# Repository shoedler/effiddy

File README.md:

# effiddy
A 50-key, column-staggered, wireless split keyboard, inspired by Totem. Designed for Choc-spacing (16.5 by 17.5mm keycaps) and 1350 Choc v1 or v2 switches.

> Kailh Choc v2 Ice Creams, Repo-included 3D printed keycaps

## Effi.. what?
/ˈɛfɪdi/

*effiddy* is a wordplay on **effigy** — a constructed symbolic figure — and *fifty*, referencing the keyboard’s 50 keys.
An **effigy** is a physical representation of an idea, identity, or belief, often ritualistic or iconic in nature.

The design and name are inspired by the **Kindlifresserbrunnen** (Child-Eater Fountain) in Bern, Switzerland:
a striking, unsettling effigy that embodies folklore, symbolism, and cultural memory.
Effiddy adopts this spirit in a minimalist, abstract form — part artifact, part tool.

> **Design note**
> This project came together as a follow up on the [shoedler54](https://github.com/shoedler/shoedler54) split and is also designed entirely in [ergogen.xyz](ergogen.xyz). Since I wanted effiddy to be as thin as possible, I modeled the backside of the case to include cutouts for the SMD components (hotswap sockets, diodes etc.) which resulted in a very thin keyboard, but also an insanely complex ergogen config. The generation of the stl files literally takes minutes when running ergogen through the browser. The reasonable approach to this would've been to use the 3d kicad model of the PCB to model the backplate in CAD. Though, you'd have to model it for both halves due to hotswap socket placement.

## Impressions

---

## Bill of materials

For one complete board - e.g. two halves - you'll need:

- 2 Promicro NRF52840
- 50 1N4148W SOD-123 Diodes
- 50 Kailh Low-profile 1350 Hotswap Sockets
- 50 Keyswitches, Choc v1 or v2
- 50 1u Choc-spaced (16.5x17.5mm) Keycaps, Choc v1 or v2 stem
- 2 EVQPUL02K Switches ($\to$ board reset button)
- 2 SSSS811101 Switches ($\to$ power switch)
- 2 701535 3.7v, 350mAh Batteries
- 2 JST PH 2.0 THT Sockets

For the case you'll need:

- Obviously, the printed case files. See section about printing below.
- 4 M2x3mm heat set inserts.
- 4 M2x6mm (or 8mm) flathead screws
- 8 Stick-on rubber feet

## Build guide

### PCB manufacturing

> PCB related files are located in the `kicad` directory.

I do not suggest rerouting the PCB for fun. There's premade gerber archive located at `kicad/gerber.zip` which you can use. I've used JLCPCB, default settings (1.6mm two layer PCB) and with the black solder mask.

> [!NOTE]
> There's also a 3d render (.stl) of the assembled PCB in the `kicad` directory if you want to model your own case.

### Printing the case

> Case files are located in the `stl` directory.

I used a Babulab A1 mini and default slicer settings (Bambustudio). Everything was printed in their PLA Matte. For a nice effect, I suggest white for the top and keycaps and black for the bottom.

#### What do I need to print?

You'll need at least:

- 2x `effiddy_case_top.stl`, which is the top part of the case where the keyswitches are mounted into - I recommend using the provided 3mf files for that: `effiddy_case_top_left.3mf` and `effiddy_case_top_right.3mf`. Which are mirrored versions with support enabled for the Mcu + Bat enclosures. (Theoretically, bridging works fine, but support is definitely easier and more predictable)
- 1x `effiddy_case_bottom_left.stl`, and
- 1x `effiddy_case_bottom_right.stl`. These are the bottom part of the case - same story, use the provided 3mf files for that: `effiddy_case_bottom_left.3mf` and `effiddy_case_bottom_right.3mf`. These are **not** just mirrored versions. The bottom part of the case is not mirrorable, due to the hotswap sockets being aligned differently for the left and right. 

> [!NOTE]
> The `effiddy_case_bottom_left.stl` and `right.stl` are generated by ergogen. Due to their complexity, they are cursed and a little bit broken. The shape is not closed, there are multiple naked edges, planar and non-planar holes as well as degenerate faces. Despite that, I had no trouble printing it in Bambustudio.

### Printing the keycaps

> Keycap related files are located in the `scad` directory.

The caps require no supports if you place them on one of the fillets - they do however require good bed adhesion. This, just like the case, was also printed on a Bambulab A1 mini with PLA Matte. Also, like the case, I've provided a 3mf file to print regular and indexing (F/J keys on QWERTY) keys. If you have to use the stl directly:

- Use 0.12mm layer height (including the initial layer).
- Use a brim - if your slicer doesn't automatically generate it, add it manually.
- Use a little manually placed support on the face of the keycap. Centered, about 1/3 the way up the slope. In Bambustudio, the slicer will turn this into a small wedge that is just enough to stabilize the cap but not leave any traces of support material on the keycap face.

> [!NOTE]
> The keycap was designed in [OpenSCAD](openscad.org). It's fully parametrized, so it's easy to adapt to your liking.

### Soldering

Since the PCB is reversible it can get confusing quick. All of the components **except the ProMicro and the JST connector** are soldered to the backside of each half.

1. Solder diodes, hotswap sockets, reset- and powerswitches on the backside of each half. **This is also the side were you bridge all of the solder-jumpers with solder** (8 for the Mcu, 2 for the Battery connector).
2. Direct-solder the ProMicro to the frontside of the PCB, along with the JST connector. (Pin Sockets are also an option for the mcu, if you want - it just makes the keyboard a bit thicker)

> [!CAUTION]
> Before you continue it's a good idea to verify that there's no short between the JSTs +/- terminal as well as the ProMicros VCC and GND.

I suggest to load the firmware next and check that everything works before assembly.

### Loading the ZMK firmware

> Firmware related files consist of: config/, boards/, zephyr/ directories, as well as the build.yml file and the GitHub Actions workflow in .github/workflows.build.yml

Get the latest firmware from https://github.com/shoelder/effiddy/actions, select the latest run and scroll down to Artifacts - you'll be able to download the zip archive from there.

> [!NOTE]
> There'll be two .uf2 files per half in the zip archive - a `de-ch` and an `en` version. This refers to the keycode locale that's been used. I myself require a swiss locale, but, to make the default firmware more useful for more people, I've added an english version too. You can check the keymaps out in the `config/boards/shields/effiddy` directory.

For each half:

1. Plug in the half to your device using a USB cable.
2. Press the reset button twice within 500ms - on my versions of the ProMicro, their red LED breaths gently once you've entered bootloader mode.
3. You'll see a `NICENANO` appear in your device tree. Simply drag and drop the **correct** firmware for the half your working on onto the mcu - it should eject itself automatically once the firmware is flashed.

> [!NOTE]
> If you run into trouble, there's also a `settings_reset` firmware provided in the archive. See [the ZMK troubleshooting guide](https://zmk.dev/docs/troubleshooting/connection-issues#reset-split-keyboard-procedure) on how to flash it.

### Assembly

1. Prep the case tops by installing the two heat set inserts and removing support material. In my case, I have used SMD JST connectors which are a bit too wide for the channel in the case which was resolved with a bit of surgery with a sharp utility knife.
2. Connect the battery. Mount the top case.
3. Install the switches and keys.
4. Flip the whole thing, tuck the battery wires into the channel.
5. Mount the back case half. Install the two screws - done!

---

## References

- Flatfootfox' detailed design guide: https://flatfootfox.com/ergogen-part1-units-points/
- nickcoutsos Keymap-editor: https://nickcoutsos.github.io/keymap-editor/
- nickcoutsos Keymap-layout-tools: https://nickcoutsos.github.io/keymap-layout-tools/
- Joel Spadins zmk-locale-generator for the de-swiss keycode header: https://github.com/joelspadin/zmk-locale-generator
- ZMK guide on how to add a new shield: https://zmk.dev/docs/development/hardware-integration/new-shield
- More of my keyboards:
  - shoedler54 - a cheap 54-key wireless split, inspired by the ZSA Voyager: https://github.com/shoedler/shoedler54

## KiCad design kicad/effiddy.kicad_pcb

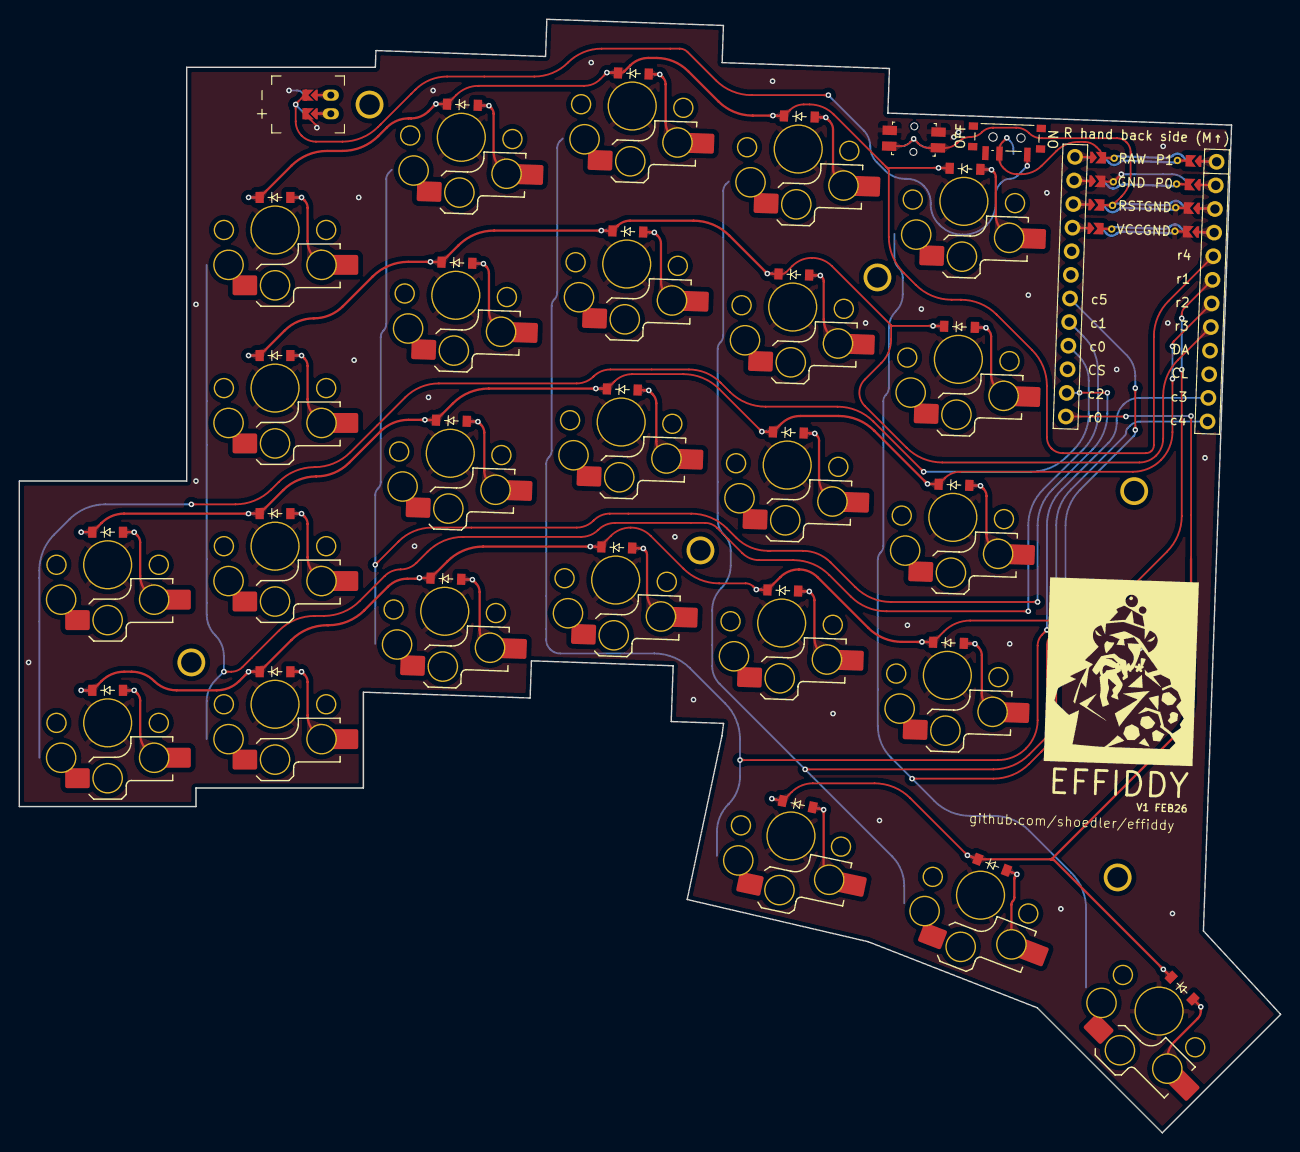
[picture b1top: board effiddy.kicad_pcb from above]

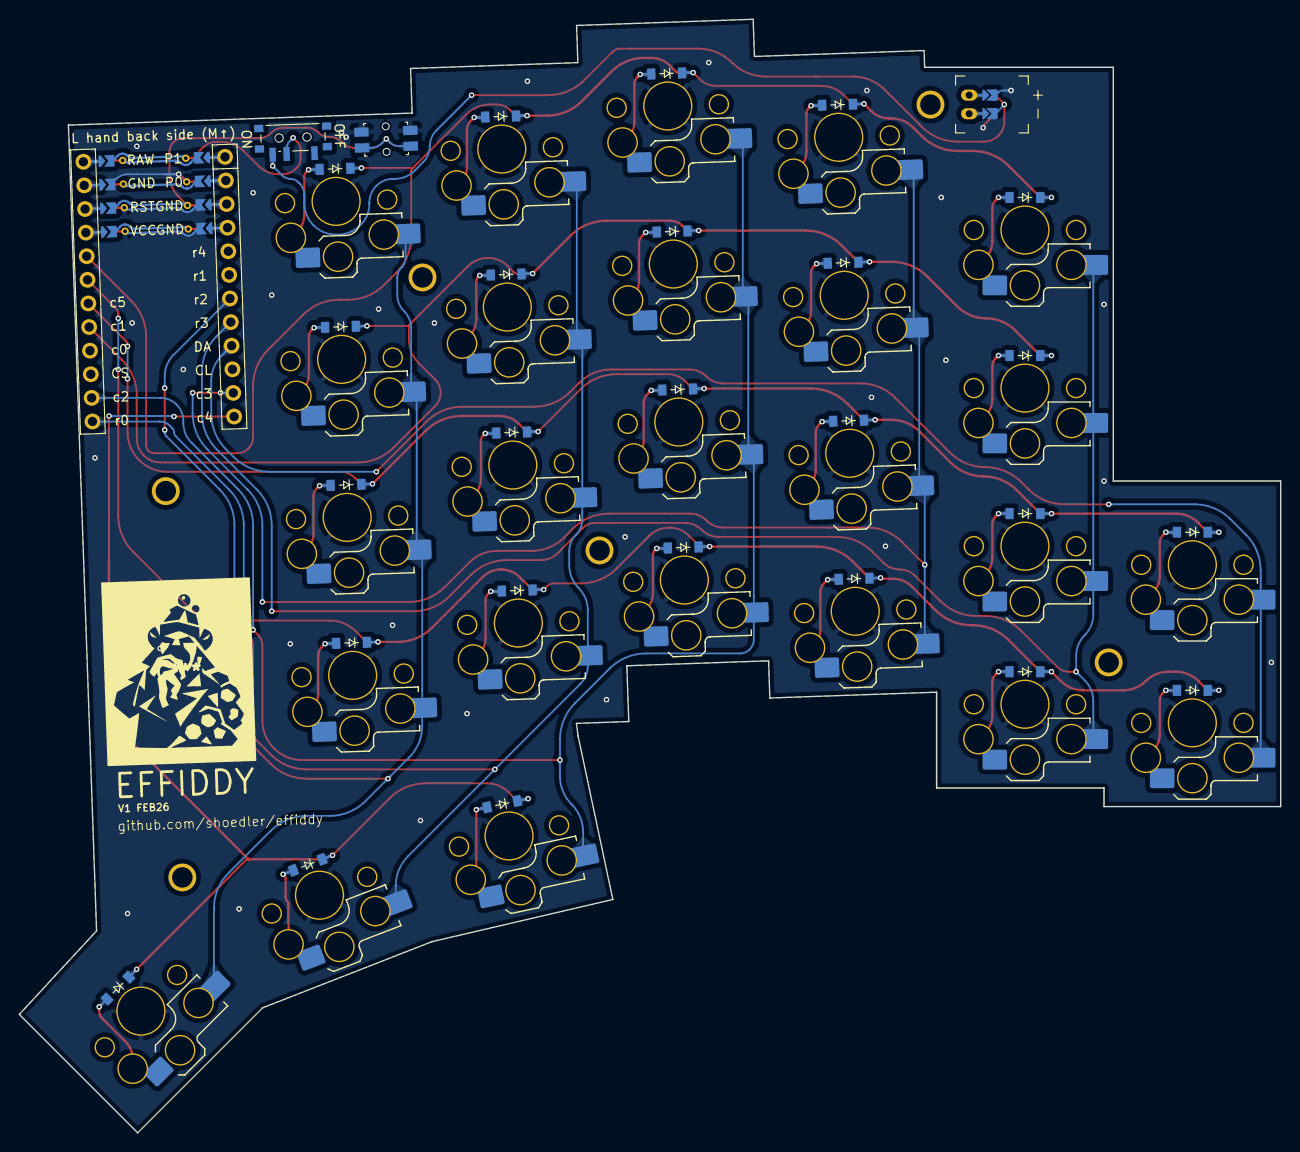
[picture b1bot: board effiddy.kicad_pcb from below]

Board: 2 copper layers, 135.6 x 119.7 mm, 60 parts (25 on the bottom side), 41 nets.

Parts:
D1, D2, D3, D4, D5, D6, D7, D8, D9, D10, D11, D12, D13, D14, D15, D16, D17, D18, D19, D20, D21, D22, D23, D24, D25: diode_tht_sod123
JST1: battery_connector_jst_ph_2
MCU1: mcu_supermini_nrf52840
MH1, MH2, MH3, MH4, MH5, MH6: mounting_hole_npth
PWR1: power_switch_smd_side
RST1: reset_switch_smd_side
S1, S2, S3, S4, S5, S6, S7, S8, S9, S10, S11, S12, S13, S14, S15, S16, S17, S18, S19, S20, S21, S22, S23, S24, S25: switch_choc_v1_v2

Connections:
GND: JST1.2, MCU1.103, MCU1.104, MCU1.123, RST1.1, RST1.3
JST1_1: JST1.11, JST1.21, JST1.31
JST1_2: JST1.12, JST1.22, JST1.32
RAW: MCU1.124, PWR1.2
RST: MCU1.122, RST1.2, RST1.4
c0: MCU1.16, S1.2, S2.2
c0_r1: D1.2, S1.1
c0_r2: D2.2, S2.1
c1: MCU1.17, S3.2, S4.2, S5.2, S6.2
c1_r1: D3.2, S3.1
c1_r2: D4.2, S4.1
c1_r3: D5.2, S5.1
c1_r4: D6.2, S6.1
c2: MCU1.14, S7.2, S8.2, S9.2, S10.2
c2_r1: D7.2, S7.1
c2_r2: D8.2, S8.1
c2_r3: D9.2, S9.1
c2_r4: D10.2, S10.1
c3: MCU1.11, S11.2, S12.2, S13.2, S14.2, S23.2
c3_r0: D23.2, S23.1
c3_r1: D11.2, S11.1
c3_r2: D12.2, S12.1
c3_r3: D13.2, S13.1
c3_r4: D14.2, S14.1
c4: MCU1.12, S15.2, S16.2, S17.2, S18.2, S24.2
c4_r0: D24.2, S24.1
c4_r1: D15.2, S15.1
c4_r2: D16.2, S16.1
c4_r3: D17.2, S17.1
c4_r4: D18.2, S18.1
c5: MCU1.18, S19.2, S20.2, S21.2, S22.2, S25.2
c5_r0: D25.2, S25.1
c5_r1: D19.2, S19.1
c5_r2: D20.2, S20.1
c5_r3: D21.2, S21.1
c5_r4: D22.2, S22.1
r0: D23.1, D24.1, D25.1, MCU1.13
r1: D1.1, D3.1, D7.1, D11.1, D15.1, D19.1, MCU1.6
r2: D2.1, D4.1, D8.1, D12.1, D16.1, D20.1, MCU1.7
r3: D5.1, D9.1, D13.1, D17.1, D21.1, MCU1.8
r4: D6.1, D10.1, D14.1, D18.1, D22.1, MCU1.5

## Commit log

2026-02-10 Init
2026-02-10 Adds banner
2026-02-10 Updates banner
2026-02-10 Compresses banner
2026-02-19 Updates pcb with 3d model, updates ergogen config
2026-02-19 Moves pcb renders
2026-02-19 Include images of effiddy PCB renders
    Add PCB render images to README
2026-02-20 Fixes shield refs.
2026-02-20 Fixes file refs.
2026-02-20 Updates bindings.
2026-02-20 Fixes keymaps.
2026-02-21 Adds keycaps
2026-02-23 Refactors PCB 3d view, updates keycap + 3mf file
2026-03-09 Adds final case files, starts README
2026-03-09 Updates case files
2026-03-09 Updates README
2026-03-09 Adds pictures
